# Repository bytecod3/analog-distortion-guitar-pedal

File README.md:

# analog-distortion-guitar-pedal
Analog distortion guitar pedal 

This is a mono analog guitar distortion pedal.

It contains a tunable low pass filter with a BW of 2KHz, gain ranging from 20dB to 40dB, an NPN transistor amplifier stage, an analog clipping circuit for waveform distortion and an output volume control knob.

Input and output is fed by a 6.35mm TRS audio jack.

### Simulations

The waveform above shows how the sinusoidal input wave is clipped into a square wave.

### Power supply

Power supply is a 9V DC split.

### 3D casing view

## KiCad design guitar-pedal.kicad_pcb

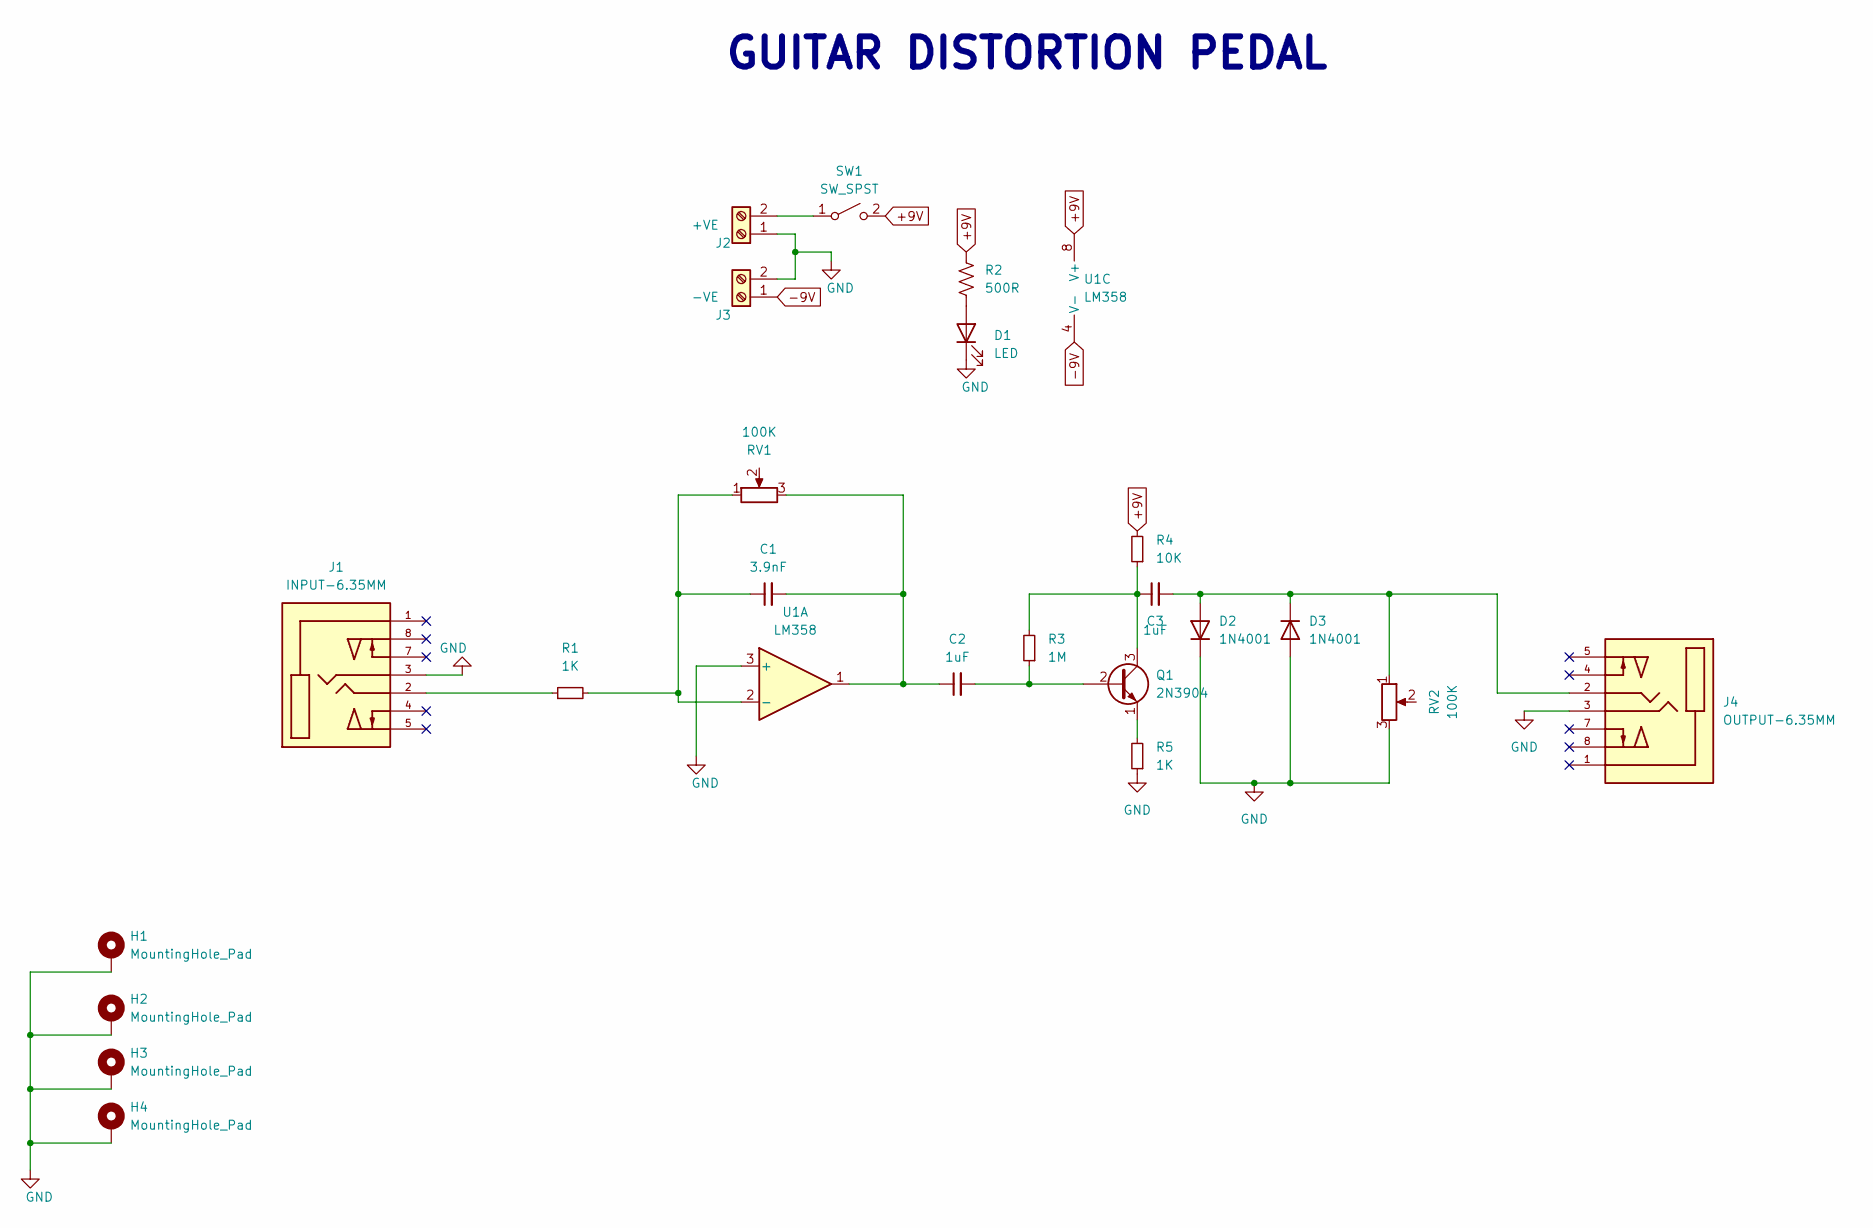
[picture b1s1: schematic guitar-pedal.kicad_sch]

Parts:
C1: 3.9nF; CP_Radial_D4.0mm_P2.00mm
C2, C3: 1uF; CP_Radial_D4.0mm_P2.00mm
D1: LED; LED_D3.0mm_Horizontal_O6.35mm_Z10.0mm
D2, D3: 1N4001; D_DO-41_SOD81_P10.16mm_Horizontal
H1, H2, H3, H4: MountingHole_Pad; MountingHole_2.7mm_M2.5_Pad_Via
J1: INPUT-6.35MM; CUI_SJ-63043H; PARTREV 1.0
J2: +VE; TerminalBlock_Altech_AK300-2_P5.00mm
J3: -VE; TerminalBlock_Altech_AK300-2_P5.00mm
J4: OUTPUT-6.35MM; CUI_SJ-63043H; PARTREV 1.0
Q1: 2N3904; TO-92_Inline
R1, R5: 1K; R_Axial_DIN0414_L11.9mm_D4.5mm_P25.40mm_Horizontal
R2: 500R; R_Axial_DIN0414_L11.9mm_D4.5mm_P25.40mm_Horizontal
R3: 1M; R_Axial_DIN0414_L11.9mm_D4.5mm_P25.40mm_Horizontal
R4: 10K; R_Axial_DIN0414_L11.9mm_D4.5mm_P25.40mm_Horizontal
RV1, RV2: 100K; Potentiometer_Alps_RK09L_Single_Vertical
SW1: SW_SPST; SW_100SP1T1B4M2QE
U1: LM358; DIP-8_W7.62mm

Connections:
+9V: R2.1, R4.2, SW1.2 (B), U1.8 (V+)
-9V: J3.1, U1.4 (V-)
GND: D1.1 (K), D2.1 (K), D3.2 (A), H1.1, H2.1, H3.1, H4.1, J1.3, J2.1, J3.2, J4.3, R5.1, RV2.3, U1.3 (+)
unnamed: C1.1, R1.2, RV1.1, U1.2 (-)
unnamed: C1.2, C2.1, RV1.3, U1.1
unnamed: C2.2, Q1.2 (B), R3.1
unnamed: C3.1, Q1.3 (C), R3.2, R4.1
unnamed: C3.2, D2.2 (A), D3.1 (K), J4.2, RV2.1
unnamed: D1.2 (A), R2.2
unnamed: J1.2, R1.1
unnamed: J2.2, SW1.1 (A)
unnamed: Q1.1 (E), R5.2

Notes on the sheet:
GUITAR DISTORTION PEDAL

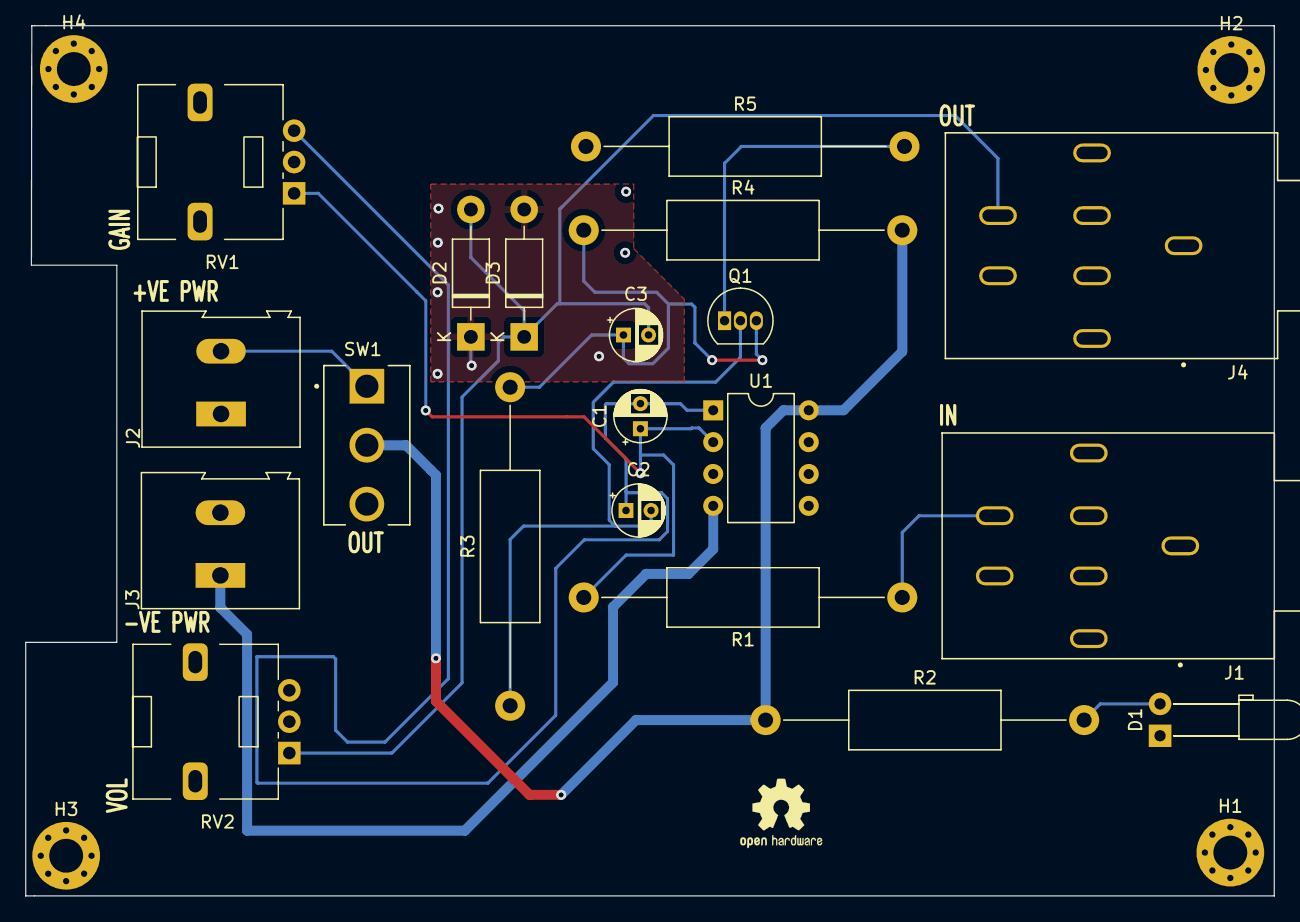
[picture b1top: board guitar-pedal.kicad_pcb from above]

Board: 2 copper layers, 99.6 x 69.4 mm, 24 parts (0 on the bottom side), 12 nets.

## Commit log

2023-04-25 Added ortho view
2024-06-14 updates README
